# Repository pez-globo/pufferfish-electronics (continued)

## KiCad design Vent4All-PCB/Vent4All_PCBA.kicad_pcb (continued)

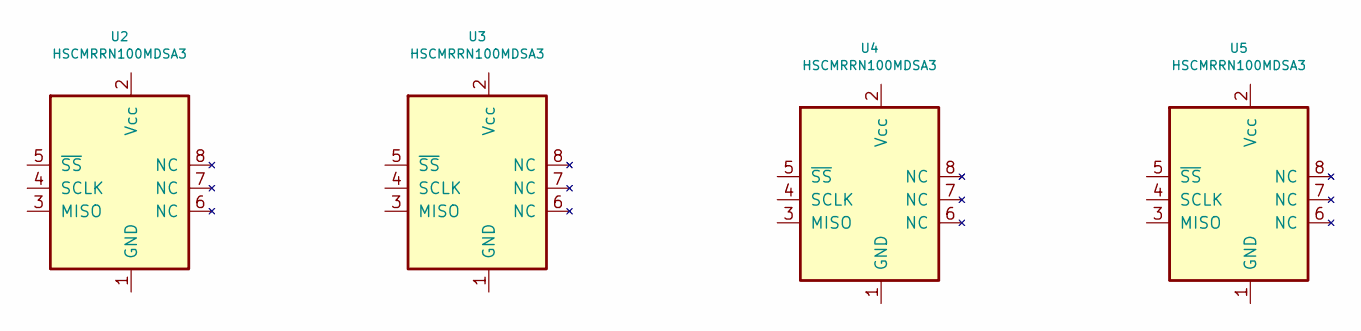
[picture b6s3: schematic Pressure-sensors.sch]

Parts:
U2, U3, U4, U5: HSCMRRN100MDSA3; HSCMRRN100MDSA3_SOIC-8

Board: 2 copper layers, 8 parts (0 on the bottom side), 8 nets, no tracks yet.

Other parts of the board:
D1: CQY99; LED_D5.0mm_IRGrey

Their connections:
LED-EN1: D1.2; also elsewhere on the board

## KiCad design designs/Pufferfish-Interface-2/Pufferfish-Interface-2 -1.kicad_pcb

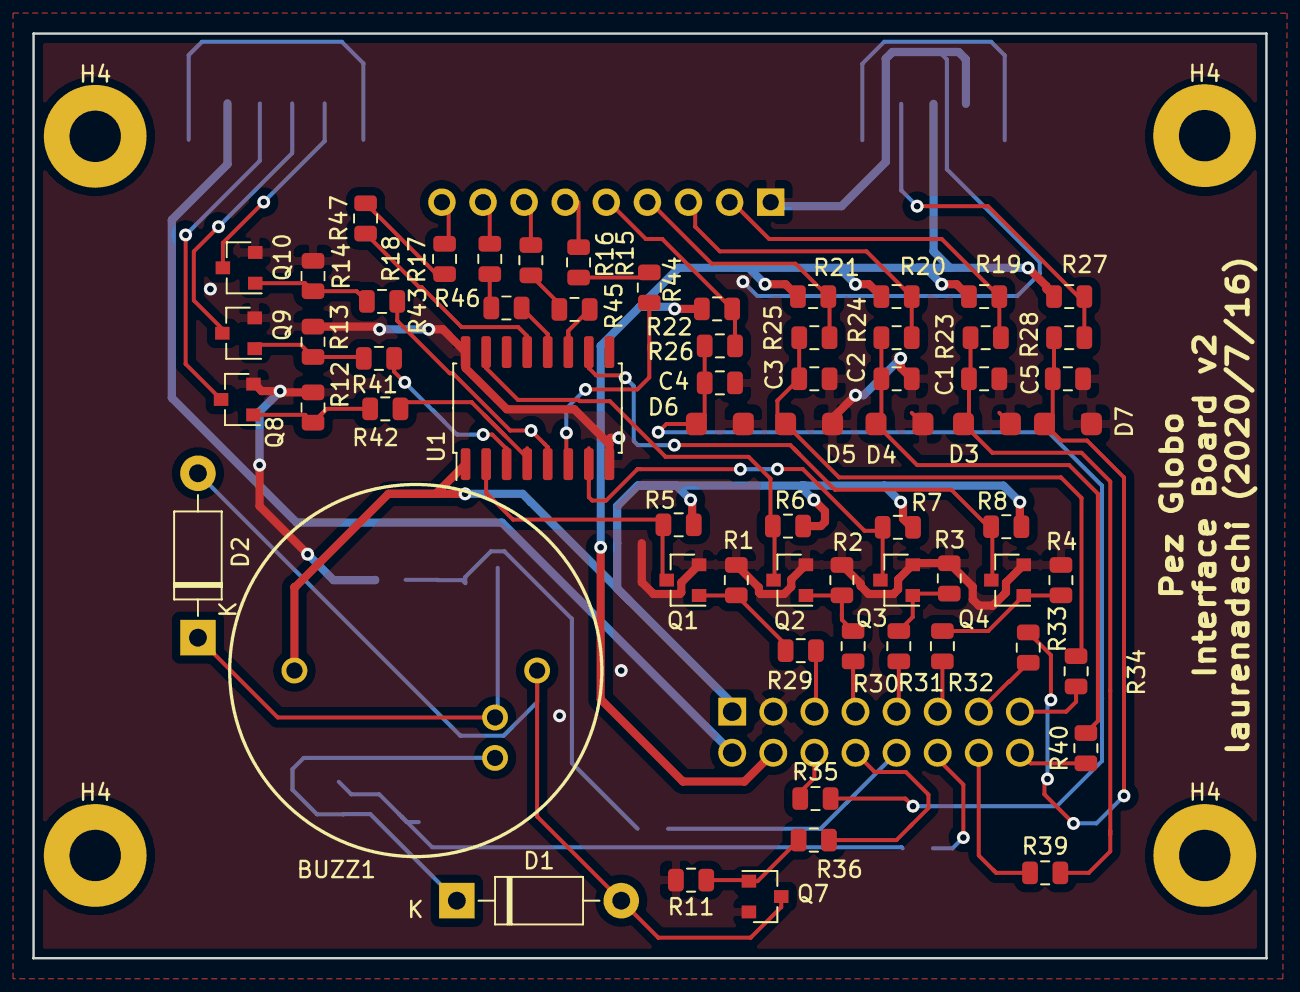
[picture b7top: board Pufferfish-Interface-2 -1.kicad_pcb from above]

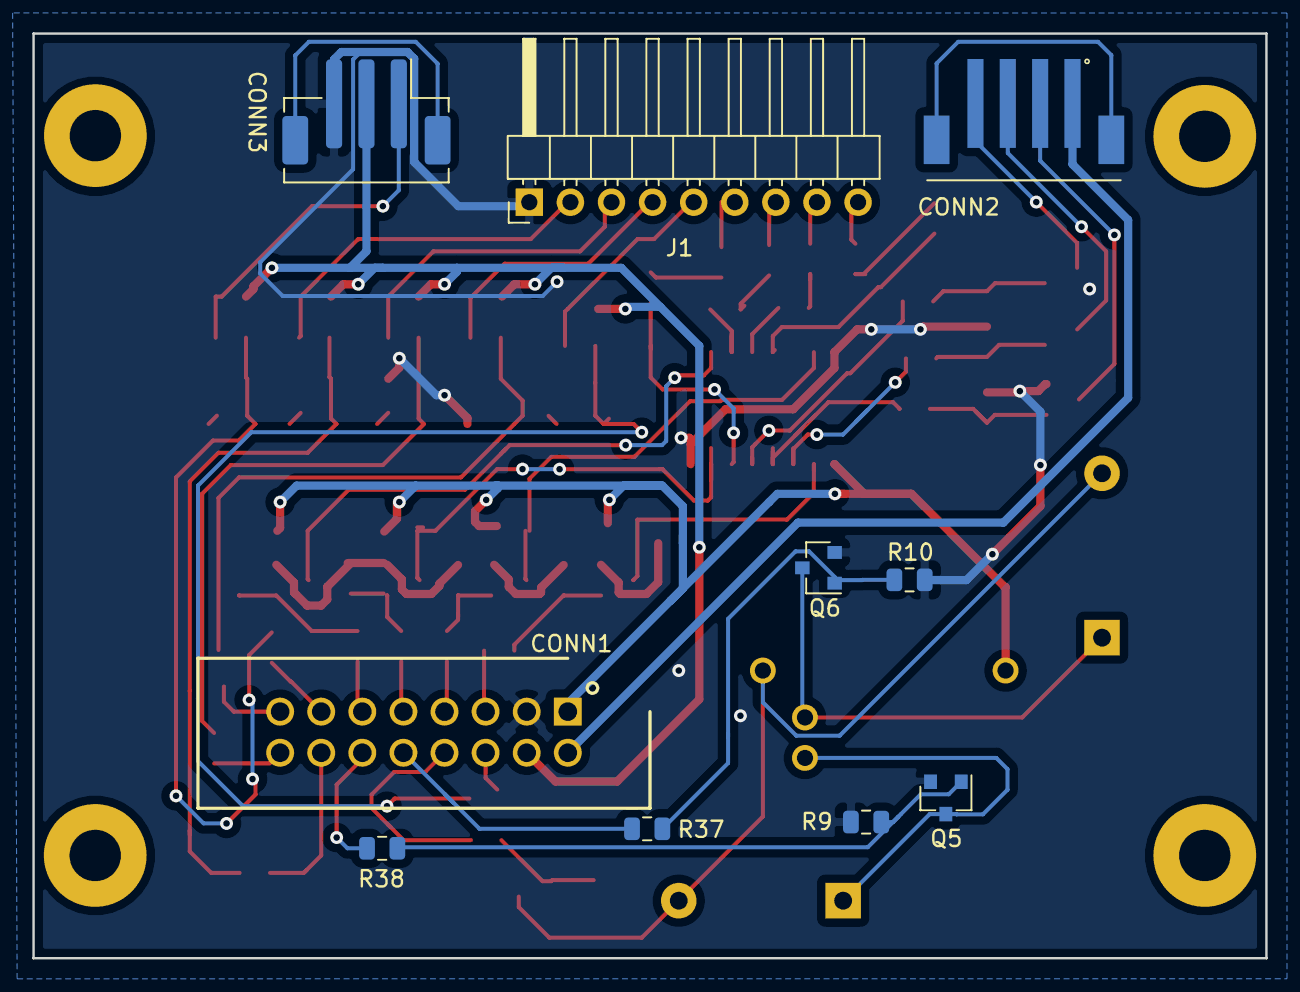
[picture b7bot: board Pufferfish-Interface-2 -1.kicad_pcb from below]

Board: 2 copper layers, 76.2 x 57.1 mm, 79 parts (10 on the bottom side), 63 nets.

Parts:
BUZZ1: BUZZER-MALLORY; Buzzer-MSS5MMG
C1, C2, C3, C4, C5: 0.1uF; CAP_SMD_0805
CONN1: 5103308-3; SHDR16W66P254_2X8
CONN2: B4B-PH-SM4-TB(LF)(SN); JST_B4B-PH-SM4-TB
CONN3: B3B-PH-SM4-TB(LF)(SN); JST_B3B-PH-SM4-TB
D1, D2: 1N4001; D_DO-41_SOD81_P10.16mm_Horizontal
D3, D4, D5, D6, D7: SMF3.3; D_TVS_SMF3.3
H4, H4#2, H4#3, H4#4: STANDOFF_ELECTRICAL-NOTHERMALS; STANDOFF-ELECTRICAL-NOTHERMALS
J1: Conn_01x09_Male; PinHeader_1x09_P2.54mm_Horizontal
Q1, Q2, Q3, Q4, Q8, Q9, Q10: 2N7002E; SOT-23
Q5, Q6, Q7: DMN10H220L; SOT-23
R1, R2, R3, R4, R5, R6, R7, R8, R9, R10, R11, R12, R13, R14, R15, R16, R17, R18, R19, R20, R21, R22, R23, R24, R25, R26, R27, R28, R29, R30, R31, R32, R33, R34, R35, R36, R37, R38, R39, R40, R41, R42, R43, R44, R45, R46, R47: RES_SMD_0805
U1: STPIC6D595; SO-16_5.3x10.2mm_P1.27mm

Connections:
3.3V: CONN1.4, CONN3.2, R19.1, R20.1, R21.1, R22.1, R27.1
5V: BUZZ1.1, CONN1.1, R5.1, R6.1, R7.1, R8.1, U1.1
+12V: CONN1.2, CONN2.1
ALARM1_HIGH: Q5.1, R9.1, R38.2
ALARM1_LOW: Q7.1, R11.1, R36.2
ALARM1_MED: Q6.1, R10.1, R37.2
GND: C1.2, C2.2, C3.2, C4.2, C5.2, CONN1.3, CONN3.3, D3.2, D4.2, D5.2, D6.2, D7.2, J1.1, Q1.2, Q2.2, Q3.2, Q4.2, Q5.2, Q6.2, Q7.2, Q8.2, Q9.2, Q10.2, R1.2, R2.2, R3.2, R4.2, R9.2, R10.2, R11.2, R12.2, R13.2, R14.2, U1.8, U1.16
LEDB_EN: Q10.1, R14.1, R43.2
LEDG_EN: Q8.1, R12.1, R42.2
LEDR_EN: Q9.1, R13.1, R41.2
unnamed: BUZZ1.2, D1.1, Q5.3
unnamed: BUZZ1.3, D2.1, Q6.3
unnamed: BUZZ1.4, D1.2, D2.2, Q7.3
unnamed: CONN1.5, R29.2
unnamed: CONN1.6, R35.1
unnamed: CONN1.7, R30.2
unnamed: CONN1.8, R36.1
unnamed: CONN1.9, R31.2
unnamed: CONN1.10, R37.1
unnamed: CONN1.11, R32.2
unnamed: CONN1.12, R38.1
unnamed: CONN1.13, R33.2
unnamed: CONN1.14, R39.1
unnamed: CONN1.15, R34.2
unnamed: CONN1.16, R40.1
unnamed: CONN2.2, Q8.3
unnamed: CONN2.3, Q9.3
unnamed: CONN2.4, Q10.3
unnamed: CONN2.5, CONN2.6
unnamed: CONN3.1, R27.2, R28.1
unnamed: CONN3.4, CONN3.5
unnamed: J1.2, R19.2, R23.1
unnamed: J1.3, R20.2, R24.1
unnamed: J1.4, R21.2, R25.1
unnamed: J1.5, R22.2, R26.1
unnamed: J1.6, R15.1
unnamed: J1.7, R16.1
unnamed: J1.8, R17.1
unnamed: J1.9, R18.1
unnamed: Q1.3, R5.2, U1.2
unnamed: Q2.3, R6.2, U1.15
unnamed: Q3.3, R7.2, U1.7
unnamed: Q4.3, R8.2, U1.10
unnamed: R41.1, U1.3
unnamed: R42.1, U1.4
unnamed: R43.1, U1.5
unnamed: R44.1, U1.6
unnamed: R45.1, U1.11
unnamed: R46.1, U1.12
unnamed: R47.1, U1.13
SER_CLK: Q2.1, R2.1, R30.1
SER_IN: Q1.1, R1.1, R29.1
SER_RCLK: Q4.1, R4.1, R32.1
SET_100_O2: C2.1, D4.1, R24.2, R40.2
SET_ALARM_EN: C1.1, D3.1, R23.2, R39.2
SET_LOCK: C4.1, D6.1, R26.2, R35.2
SET_MANUAL_BREATH: C3.1, D5.1, R25.2, R34.1
SET_PWR_ON_OFF: C5.1, D7.1, R28.2, R33.1
SW1_LED: R15.2, R44.2
SW2_LED: R16.2, R45.2
SW3_LED: R17.2, R46.2
SW4_LED: R18.2, R47.2
~SER_CLR: Q3.1, R3.1, R31.1

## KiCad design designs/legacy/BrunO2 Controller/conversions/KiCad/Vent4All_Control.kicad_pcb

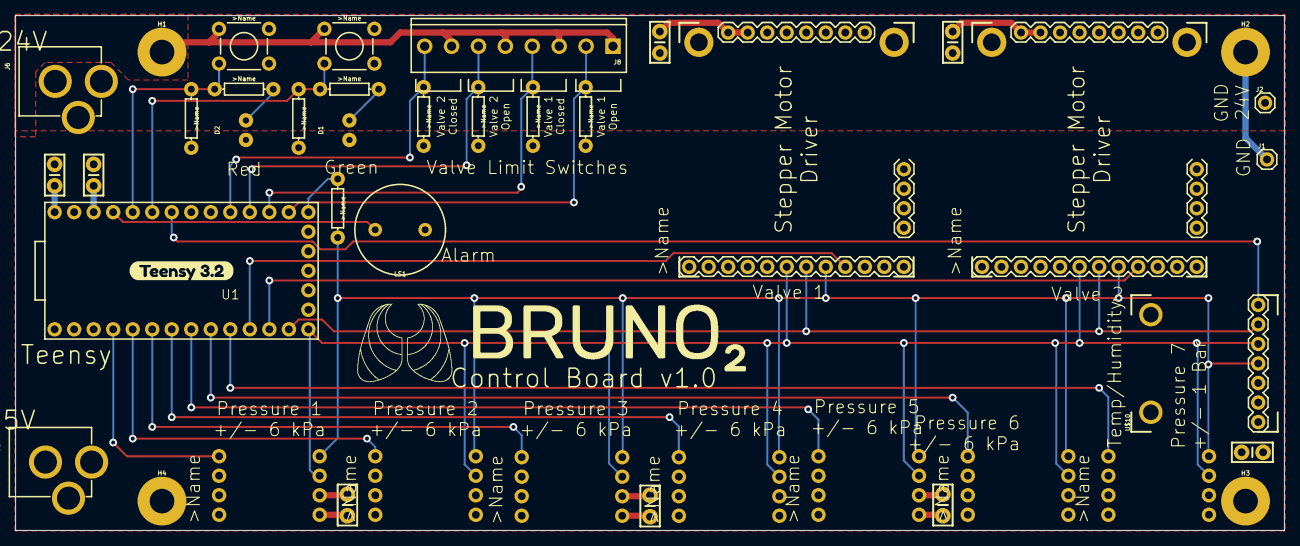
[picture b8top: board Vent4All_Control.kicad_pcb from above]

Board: 2 copper layers, 165.1 x 67.0 mm, 43 parts (0 on the bottom side), 28 nets.

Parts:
C1, C2, C5, C6, C7, C8: 0.1uF; CAP-PTH-SMALL-KIT
C3, C4: 0.1uF 50V; CAP-PTH-SMALL-KIT
D1: GREEN; LED_5MM-KIT-NO-SILK
D2: RED; LED_5MM-KIT-NO-SILK
H1, H2, H3, H4: STANDOFF_ELECTRICAL-NOTHERMALS; STANDOFF-ELECTRICAL-NOTHERMALS
J1, J2: CONN_01; 1X01
J3, J6: POWER_JACK; POWER_JACK_PTH
J8: CONN-8-3.5MM_SCREW; SCREWTERMINAL-3.5MM-8
LS1: BUZZER-PTH; BUZZER-12MM
R1, R2: 470; AXIAL-0.3
R3, R4, R5, R6, R7, R8: 4.7k; AXIAL-0.3
R9: 25; AXIAL-0.3
S1, S2: MOMENTARY-SWITCH-SPST-PTH-6.0MM; TACTILE_SWITCH_PTH_6.0MM
U1: TEENSY-3.2PTH; TEENSY_TEENSY-3.2-PTH
U$1, U$2: POLOLU_36V4-MOUNTED; POLOLU_36V4
U$3, U$4, U$5, U$6, U$7, U$8: HSC_PRESSURE_SPI-HSCMRRN060MDSA3; HSC_PRESSURE_DIP
U$9: HSC_PRESSURE_SPI-HSCDRRN001BDSA3; HSC_PRESSURE_DIP
U$10: ADAFRUIT_BME280-BREAKOUT; ADAFRUIT_BME280
U$11: LOGO-BRUNO2; BRUNO2_LOGO

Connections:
3.3V: C2.1, C5.1, C6.1, C7.1, C8.1, D1.A, D2.A, R3.P$2, R4.P$2, R5.P$2, R6.P$2, R7.P$2, R8.P$2, U1.3.3V, U1.3.3V-1, U$1.2, U$1.10, U$2.2, U$2.10, U$3.2, U$4.2, U$5.2, U$6.2, U$7.2, U$8.2, U$9.2, U$10.1
5V: C1.1, J3.PWR, U1.VIN
/BUZZER: LS1.+, U1.23
/CS_BME280: U1.20, U$10.7
/CS_M1: U1.9, U$1.9
/CS_M2: U1.10, U$2.9
/CS_PS1: U1.2, U$3.5
/CS_PS2: U1.3, U$4.5
/CS_PS3: U1.4, U$5.5
/CS_PS4: U1.5, U$6.5
/CS_PS5: U1.6, U$7.5
/CS_PS6: U1.7, U$8.5
/CS_PS7: U1.8, U$9.5
/GND_24: C3.2, C4.2, J2.1, J6.GND, J6.GNDBREAK, U$1.21, U$1.22, U$1.MOUNT_1, U$1.MOUNT_2, U$2.21, U$2.22, U$2.MOUNT_1, U$2.MOUNT_2
/LED_GREEN: R1.P$1, R3.P$1, S1.3, U1.21
/LED_RED: R2.P$1, R4.P$1, S2.3, U1.22
/MISO: U1.12, U$1.6, U$2.6, U$3.3, U$4.3, U$5.3, U$6.3, U$7.3, U$8.3, U$9.3, U$10.5
/MOSI: U1.11, U$1.7, U$2.7, U$10.6
/SCK: R9.P$2, U$1.8, U$2.8, U$3.4, U$4.4, U$5.4, U$6.4, U$7.4, U$8.4, U$9.4, U$10.4
/VALVE1_C: J8.4, R6.P$1, U1.15
/VALVE1_O: J8.2, R5.P$1, U1.14
/VALVE2_C: J8.8, R8.P$1, U1.17
/VALVE2_O: J8.6, R7.P$1, U1.16
GND: C1.2, C2.2, C5.2, C6.2, C7.2, C8.2, H1.P1, H2.P1, H3.P1, H4.P1, J1.1, J3.GND, J3.GNDBREAK, J8.1, J8.3, J8.5, J8.7, LS1.-, S1.1, S2.1, U1.AGND, U1.GND, U1.GND1, U$1.3, U$2.3, U$3.1, U$4.1, U$5.1, U$6.1, U$7.1, U$8.1, U$9.1, U$10.3
unnamed: D1.K, R1.P$2
unnamed: D2.K, R2.P$2
unnamed: R9.P$1, U1.13
VIN: C3.1, C4.1, J6.PWR, U$1.23, U$1.24, U$2.23, U$2.24

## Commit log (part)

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2020-05-05 adding the original PCB made by Marc for reference
2020-05-05 Added the Squid Motion Plane for reference.
    This design comes from the Octopi microscope project, which uses a stack of boards (connected by stacking headers) for different modules. This module is used for controlling stepper motors.
2020-05-10 Initial Vent4All PCBA project upload: - Part libraries imported mostly from BrunO2_ControlBoard_v1 Eagle - Added HSC SMT pressure sensor - Imported Nucleo 144 CAD symbol and footprint - Prepared page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
2020-05-11 Added global labels for reserved communication lines (SPI, I2C, UARTs).
    Added hierarchical sheet for external connection interfaces (e.g. to RPi).
    Changed symbol libraries table to use ${KIPRJMOD} instead of absolute paths.
    When I imported the schematic, KiCAD made a rescue library and changed the line endings of all the .sch files.
2020-05-11 Backlink to CADLAB.io has been added.
2020-05-12 Added schematic connections for HSC sensors.
    Note: this assumes HSC sensors will be soldered directly to the PCB. If we are placing them on daughter boards then we will need to choose the pin header connectors and move the HSC symbols into a se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
2020-05-12 cleaned up reference design folder
2020-05-12 renamed folders
2020-05-12 moved legacy boards into their own folder
2020-05-12 reorganized structure of pufferfish board directories
2020-05-13 added gitignore to prevent cached KiCad files from syncing to the repo
2020-05-13 organizing designs (a)
2020-05-13 organizing designs (b)
2020-05-13 organizing designs (c)
2020-05-13 organizing designs (d)
2020-05-13 removed migrated files
2020-05-13 initialized controller schematics
2020-05-14 added pressure sensors
2020-05-14 started adding peripherals
2020-05-14 update gitignore
2020-05-14 part library updates
2020-05-15 added todos
2020-05-18 - Added Pufferfish logo to KiCad template - Started Power schematic - Added LTC4421 to library - Added a few capacitors to design - Added placeholder FETs (will select carefully soon)
2020-05-18 updated schematic pages to use the Pufferfish template page
2020-05-18 Revert "Update readme.md"
    This reverts commit 6df79e134eb719041ca3817e46a5f42400d368b0.
2020-05-19 added motor drivers
2020-05-19 added solenoid drivers
2020-05-19 updated controller schematics
2020-05-19 Changed library and template directories to relative paths for portability
2020-05-20 added the rest of the sensors and drivers
2020-05-20 updated controller nets and added interface board project
2020-05-20 updated oxygen sensor readout circuit
2020-05-21 - Updated thresholds for LTC4421 circuit - Added inputs page - Added passives to library
2020-05-26 - Finished LTC4421 Design - Added Input power path - Updated libraries - Added pages for interface connectors and 24V Boost
2020-06-02 updated actuators, MCU connections, and headers
2020-06-02 updates pin assignments and added CSV list of pin assignments
2020-06-03 added ports and parts for I2C pressure sensors
2020-06-03 updated pin list
2020-06-03 added onboard power regulators and power jack
2020-06-03 updated pin assignment list
2020-06-03 alarm, LEDs, switches
2020-06-04 updated pins
2020-06-05 various updates since ENGN alignment meeting
    - removed the optional instrumentation amplifier
    - added the option to populate 5V instead of 3.3V for the EK-P4 sensors (so SFM3000 could be used instead)
    - provided a separate I2C line for the O2 sensor which max'es out its communication at 100kHz
    - changed MCU pins for the solenoid driver from GPIO to PWM
2020-06-05 updated MCU pin assignment list
2020-06-05 transistors driving LEDs and debouncing
2020-06-06 - Added 3.3V and 5V Buck designs - Added interface connectors - Added voltage measurement circuit - Added preliminary charging circuit
2020-06-06 Added Components to the library
2020-06-09 separate sheets, added memory chip
2020-06-11 - Changed polarity of active low LED indicators - Added footprints for test points, inductors and mounting holes - Added ESD protection on interface connectors
2020-06-11 Generated BOM of current design
2020-06-11 completed draft w/ checked pin assignments
2020-06-11 updated title
2020-06-11 rest of titles added
2020-06-11 changed buzz pin
2020-06-12 post-review changes
    new alarm, memory pullups and capacitors (ready to be transferred to control board), EDS protection for switches, new pin assignments to support new alarm
2020-06-12 updated connectors and headers
2020-06-12 provided software controlled 5V supply to SFM3000
2020-06-12 various pin and connector updates
    * updated flow sensor and terminal footprints to use JST plug in headers
    * allocated pins for MCU to power board communication (see pin assignments)
    * connected battery power supply measurement output to one of the MCUs ADC
    * updated the VIO for the TMC2209 motor driver modules from 5V to 3.3V
2020-06-14 update pin names
2020-06-14 connector update, library update
2020-06-14 interface library
2020-06-15 added memory chip (migrated from interface board) and rounting to interface board
2020-06-15 new transistors and buzzer diodes
2020-06-15 renaming parts
2020-06-15 updated pin assignment list, generated part references, added schematic PDF
2020-06-17 added MCU connections to interface board connector and fixed power supply pin labels
2020-06-18 connector added, buzz1 transistors new, buzz1 diodes selected
2020-06-18 rev1
2020-06-18 placed control components on PCB
2020-06-19 new footprints (most)
2020-06-19 fix pin assignments
2020-06-19 all footprints except for push button
    fixed connector to M
2020-06-19 multiple LEDs option added
2020-06-19 multicolor LED footprint
2020-06-19 placed majority of components within target board size
2020-06-19 updated footprints
2020-06-22 partial fix libraries
2020-06-22 added ground and power planes
2020-06-22 library update
2020-06-22 beginning layout
2020-06-23 autorouted traces using FreeRouting.jar
2020-06-23 placement started
2020-06-23 pdf name changes
2020-06-23 touched up routing and layed out power planes
2020-06-23 completed PCB layout
2020-06-24 added SMT header option for mounting the motor driver
2020-06-25 new switches and pcb layout started
2020-06-25 if we need light-up
2020-06-26 final schematic but footprint for sw_spst_led is messed up
2020-06-26 library problem fixed
2020-06-26 board layout in progress
2020-06-26 moved one of the unused GPIO pins from the jumper to the interface board connector
2020-06-26 first board layout part placement
2020-06-29 minor pcb updates and folder organization
2020-06-29 generated Gerber files for submission to AdvancedCircuits
2020-06-29 moved around silkscreen labels and added BOM
2020-06-30 added electrolytic capacitorss to drivers and regenerated fabrication files
2020-06-30 updated BOM
2020-06-30 added the current permissive license
    License Terms You Accept by Accessing the Materials_23-June-2020.pdf
2020-06-30 first compete layout
2020-06-30 move via to pass drc
2020-06-30 zip and gerber files
2020-07-01 pcb update
2020-07-01 TVS diode update (passes DFM)
2020-07-02 added SamacSys attribution to PCB part libary readme
2020-07-02 cleaned up BOM
2020-07-02 Initial board layout, routing completed
2020-07-03 - Added gerbers - Updated layout with silkscreen and DRC
2020-07-03 - Updated track width per DFM recommendations
2020-07-03 - Updated gerbers per DFM improvements - Added current BOM - Export 3D STEP model - Updated 3D image
2020-07-03 Moved schematics to export folder
2020-07-09 interface 2 schematic started
2020-07-09 reformatting
2020-07-10 mcu serial control option for LEDs
2020-07-14 part placement interface-2
2020-07-14 moved speaker
2020-07-14 added interactive bill of materials and pick-and-place files
2020-07-15 prep for holes
2020-07-16 traces interface-2
2020-07-17 layout interface
2020-07-17 Updated schematic for new undervoltage values (10V UVF, 11V UVR) Exported schematic to PDF to reflect changes Fixed part number typo on C8
2020-07-23 new gerbers
2020-07-24 added resistors as per chris edits
2020-07-25 version ordered V2 - need to annotate schematic
2020-07-29 - Fixed footprint error for Q1-Q4 (PowerPak SO-8) - Updated gerbers with fix - Updated SMT files with fix
2020-07-29 Update LICENSE
2020-07-29 added copyrights
2020-08-04 assembly changes (footprint, etc)
2020-08-10 MOSFET update
    should fix buzzer issue
2020-08-18 J1 update to new one that fits
2020-08-18 gerber files for v2-1 w J1 update
2020-08-28 before adding the microphone
2020-08-28 starting v2-2 schematic - has voltage regulator
    removed prototype resistors
    add microphone ckt
2020-08-28 moving around
2020-08-31 add buzzer and started accomodating 6 buttons
2020-09-02 updated schematic, pre-new board layout
    barrel shifter driving changes (MOSFETs)
2020-09-03 before change to remove power switch
2020-09-03 almost complete layout
2020-09-03 finished layout, began new bom
2020-09-10 production changes
2020-09-19 cleaning up and BOM update
2020-09-25 buzzer terminal bug fix
2020-10-01 before reassigning membrane footprint
2020-10-01 added direction circle, exported gerbers
2020-10-01 updated alarm schematic with power chip
2020-10-01 new LED connector (gerber 13)
2020-10-01 added footprints for microphone ckt fix
2020-10-01 microphone layout
2020-10-21 Added LTC4015 circuit and started changing topology to agreed upon architecture for power board.
2020-10-27 config test on new account
2020-10-27 Added Molex Footprints
2020-10-27 Added Footprints
2020-10-27 Corrected Power and signal pin names
2020-10-27 Basic LTC2955 schema done
2020-10-30 Added library files for LTC2955
2020-11-01 Created 172287120 footprint
2020-11-02 Created footprints for Molex
2020-11-02 Removed older design schematics
2020-11-02 Created 2 Design files for HMI and MCU
2020-11-03 Corrected capacitor values for LTC2955
2020-11-07 LTC2955 1st review
2020-11-08 Barebone config solderpads for LTC7812
2020-11-09 Minor changes
2020-11-12 minor changes, rechecked values
2020-11-12 Added LTC7812 Boost 24V
2020-11-14 Minor changes.
2020-11-15 Corrected footprints, minor changes in nets
2020-11-15 Fixed footprints
2020-11-15 Fixed 7812 symbol bug
2020-11-17 Board setup, 3.3V regulator placement
2020-11-17 Minor reference changes
2020-11-18 Placement changes
2020-11-19 Placements updated
2020-11-20 Updated placement
2020-12-02 Revised placement as per feedback
2020-12-05 Extended PCB size to accommodate the standoffs added
2020-12-06 4015 Minor changes
2020-12-09 Finished LTC4015 Initial circuit
2020-12-09 added LTC4015
2020-12-09 Added NTC Connection
2020-12-10 Changed LTC4015 I2C digital levels to INTVCC instead of 3.3V
2020-12-11 Added voltage translator(I2C), changed 12V Labels for step down conv
2020-12-14 Finalized and corrected footprints
2020-12-15 Updated the LTC4015 placement. Placement Draft_1
2020-12-16 Minor updates to placement
2020-12-16 Updated schematics based on review slides. Snub and gate Res pending
2020-12-16 Minor Routing updates
2020-12-17 Routing LTC4015_1
2020-12-17 STEP file and corrected PCB dimensions
2020-12-18 Increased Drill placements
2020-12-21 Updated Routing
2020-12-22 Updated routing 2
2020-12-22 Minor updates to routing
2020-12-23 Updated Routing -3
2021-01-02 Updated routing and copper pours
2021-01-03 Minor routing
2021-01-04 Added pours on all layers, minor changes
2021-01-05 Routing completed, stitching pending
2021-01-06 Updated stitching
2021-01-11 Fixed minor DRC issues
2021-01-14 Added fiducialmarkers and PGOOD for 5v,3V3
2021-01-14 Schematic annotation
2021-01-31 Deepak schematics updated
2021-01-31 Reworked placements
2021-02-02 Reverted to commit: e75bf60, increased board dim. by 5mm to place JST. REV2
2021-02-03 Minor changes to routing
2021-02-07 Completed routing
2021-02-07 Corrected Major DRC Issues
2021-02-12 Updated routing, review pending
2021-02-18 Generated GBR files for review
2021-02-19 Created BOM, added MPNs
2021-02-26 Generated BOM and placement files
2021-03-14 Resolving Exceptions, Pending #7
2021-03-18 Resolved Exceptions
2021-03-19 Resolved the exception completely
2021-03-26 Reslolved recent exception fully
2021-08-30 Removed redundant files
